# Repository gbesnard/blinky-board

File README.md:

# Blinky board

Simple blinking board using a 555 timer. 

PCB designed using EAGLE.

## Schematics

## Pictures

## Blinking period

t1 = 0.693 (R1 + R2) * C2 = 0.693 (1000 + 100 000) * 22*10^-6 = 1.53

t2 = 0.693 (R2) * C2 * 22 * 10^-6 = 1.53

Period = t1 + t2 = 3 sec

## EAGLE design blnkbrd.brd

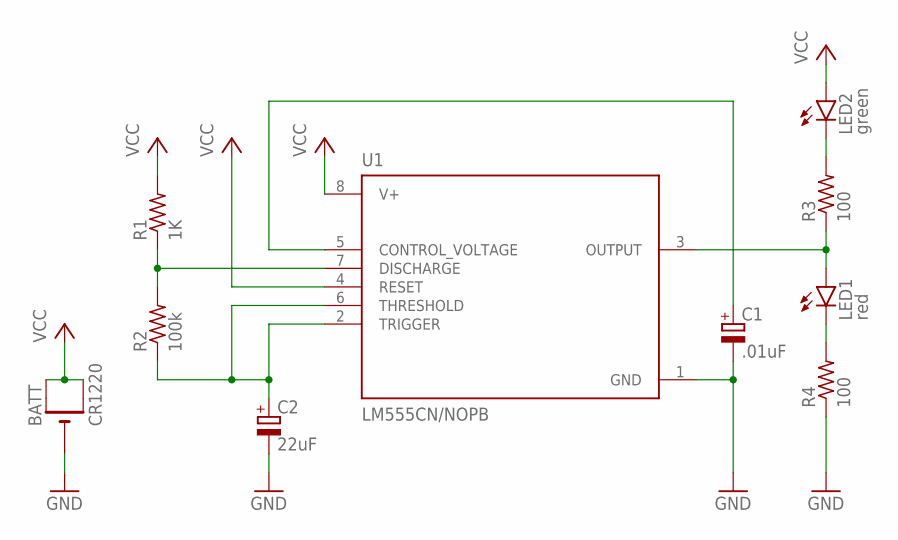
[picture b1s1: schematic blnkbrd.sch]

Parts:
BATT: CR1220; CR1220-SMD
C1: .01uF; E2,5-6E
C2: 22uF; E2,5-6E
LED1: red; LED3MM
LED2: green; LED3MM
R1: 1K; 0207/10
R2: 100k; 0207/10
R3, R4: 100; 0207/10
U1: LM555CN/NOPB; DIP794W45P254L959H508Q8

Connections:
CONN: C2.+, R2.1, U1.2 (TRIGGER), U1.6 (THRESHOLD)
GND: BATT.-, C1.-, C2.-, R4.1, U1.1 (GND)
unnamed: LED2.K (C), R3.2
unnamed: LED1.A, R3.1, U1.3 (OUTPUT)
unnamed: LED1.K (C), R4.2
unnamed: R1.1, R2.2, U1.7 (DISCHARGE)
unnamed: C1.+, U1.5 (CONTROL_VOLTAGE)
VCC: BATT.+$1 (+), BATT.+$2 (+1), LED2.A, R1.2, U1.4 (RESET), U1.8 (V+)

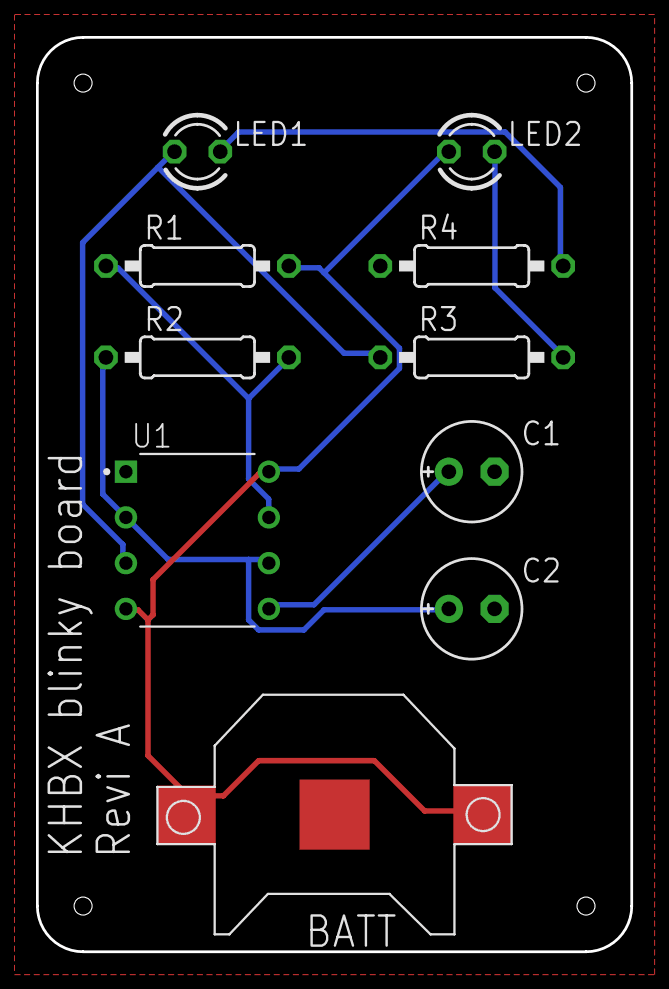
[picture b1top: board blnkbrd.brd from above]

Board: 2 copper layers, 33.0 x 50.8 mm, 10 parts (0 on the bottom side), 8 nets.

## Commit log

2021-10-30 add eagle files and pictures
